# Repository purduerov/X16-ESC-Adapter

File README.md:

# Readme for X16-ESC-Adapter
This board powers the ESCs and routes signals to and from the ESCs.

Whenever you make a new part, download the datasheet and save it here _**and**_ with the part in the parts library

Always pull other people's changes before beginning to work
`git pull`

Be sure to push your changes after  working on them. Run:
1. `git add .` to add any files in this directory or a subdirectory
or `git add -u` to add any modified files
2. (Optional) `git clean -nX` to see what ignored files can be removed
	`git clean -fX` removes ignored files (Eagle backups)
3. `git commit -m "helpful commit message"` with a description of the work that you did
4. `git push` to push your work to github

Other helpful commands
* `git status` says information about modified and staged files
* `git log` shows the recent commits of the repository
* `git log filename.extension` show the recent commits for just that file
* `git checkout first-couple-letter-of-commit-id` lets you go back to a previous version
* `git checkout master` brings you back to the latest commit
* `git tag` lists the tags
* `git tag -a orderX -m "the version of the board placed for the X'th order"` tag a specific commit
* `git push --tags` needed to push tags to remote
* `git show orderX` show the commit log for the given tag
* `git checkout orderX` go back and interact with the files at the tagged commit

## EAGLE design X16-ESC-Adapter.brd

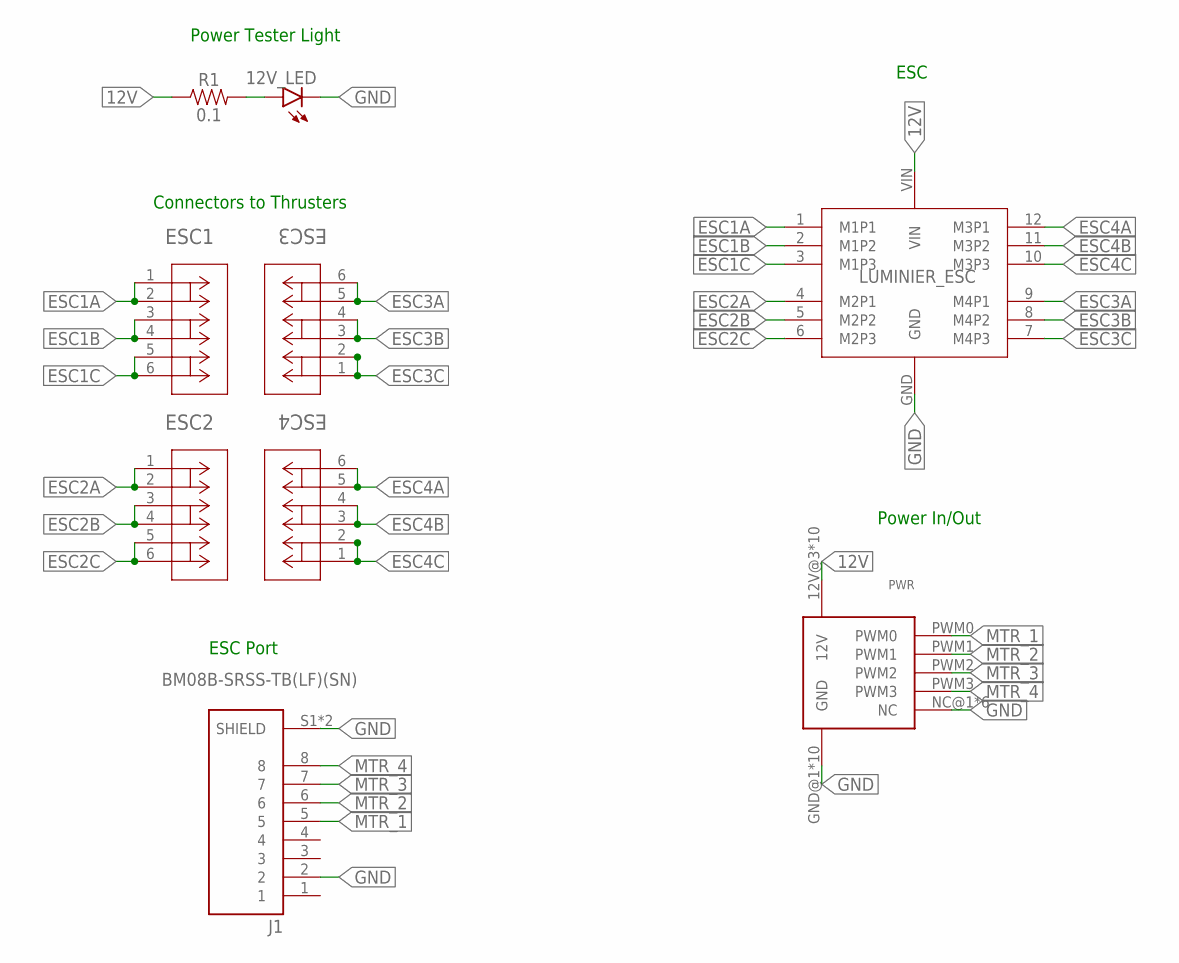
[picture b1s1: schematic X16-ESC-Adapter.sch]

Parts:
12V_LED: LEDCHIPLED_0805; CHIPLED_0805
ESC1, ESC2, ESC3, ESC4: CONN_1824750000; CONN3_1824750000_WED
J1: BM08B-SRSS-TB(LF)(SN); JST_BM08B-SRSS-TB(LF)(SN)
LUMINIER_ESC: LUMENIER
PWR: CONN_BACKPLANE_ESC_ADAPTER
R1: 0.1; 0603

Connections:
12V: LUMINIER_ESC.VIN, PWR.12V@3 (12V), PWR.12V@4 (12V), PWR.12V@5 (12V), PWR.12V@6 (12V), PWR.12V@7 (12V), PWR.12V@8 (12V), PWR.12V@9 (12V), PWR.12V@10 (12V), PWR.12V@11 (12V), PWR.12V@12 (12V), R1.1
ESC1A: ESC1.1, ESC1.2, LUMINIER_ESC.1 (M1P1)
ESC1B: ESC1.3, ESC1.4, LUMINIER_ESC.2 (M1P2)
ESC1C: ESC1.5, ESC1.6, LUMINIER_ESC.3 (M1P3)
ESC2A: ESC2.1, ESC2.2, LUMINIER_ESC.4 (M2P1)
ESC2B: ESC2.3, ESC2.4, LUMINIER_ESC.5 (M2P2)
ESC2C: ESC2.5, ESC2.6, LUMINIER_ESC.6 (M2P3)
ESC3A: ESC3.5, ESC3.6, LUMINIER_ESC.9 (M4P1)
ESC3B: ESC3.3, ESC3.4, LUMINIER_ESC.8 (M4P2)
ESC3C: ESC3.1, ESC3.2, LUMINIER_ESC.7 (M4P3)
ESC4A: ESC4.5, ESC4.6, LUMINIER_ESC.12 (M3P1)
ESC4B: ESC4.3, ESC4.4, LUMINIER_ESC.11 (M3P2)
ESC4C: ESC4.1, ESC4.2, LUMINIER_ESC.10 (M3P3)
GND: 12V_LED.C, J1.2, J1.S1 (SHIELD), J1.S2 (SHIELD), LUMINIER_ESC.GND, PWR.GND@1 (GND), PWR.GND@2 (GND), PWR.GND@3 (GND), PWR.GND@4 (GND), PWR.GND@5 (GND), PWR.GND@6 (GND), PWR.GND@7 (GND), PWR.GND@8 (GND), PWR.GND@9 (GND), PWR.GND@10 (GND), PWR.NC@1 (NC), PWR.NC@2 (NC), PWR.NC@3 (NC), PWR.NC@4 (NC), PWR.NC@5 (NC), PWR.NC@6 (NC)
MTR_1: J1.5, PWR.PWM0
MTR_2: J1.6, PWR.PWM1
MTR_3: J1.7, PWR.PWM2
MTR_4: J1.8, PWR.PWM3
unnamed: 12V_LED.A, R1.2

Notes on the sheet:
Connectors to Thrusters
Power Tester Light
Power In/Out
ESC
ESC Port

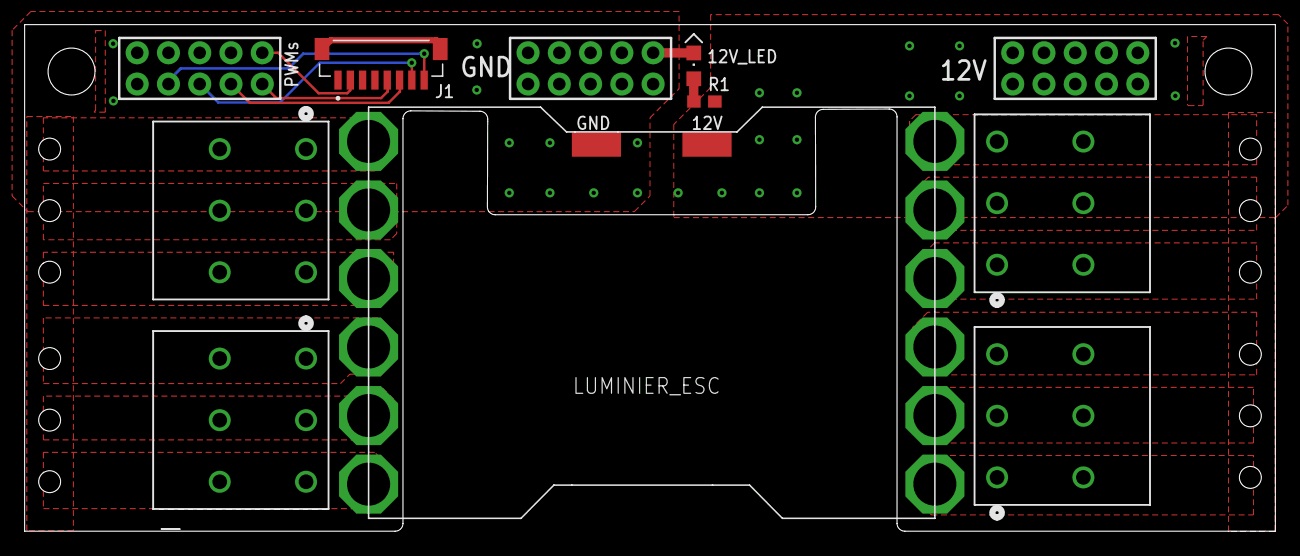
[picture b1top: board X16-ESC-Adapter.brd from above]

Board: 2 copper layers, 101.6 x 41.1 mm, 11 parts (0 on the bottom side), 19 nets.

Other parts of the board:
U$1, U$2: 6-32-HOLE

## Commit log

2023-08-30 tentative dimensions
2023-09-23 Added .gitignore file
2023-09-23 Included the needed parts
2023-10-04 Curren tprogress on schem
2023-10-04 Fixed gitignore not pulling
2023-10-04 Update X16-ESC-Adapter.brd
    10/4/23 - Started Board Circuitry
2023-10-14 Finished Layout
2023-11-02 First set of changes after alumni design review
2023-11-04 Updated (11/4)
2023-11-17 Scaffolding holes updated
    Scaffolding holes updated
2023-12-02 Finished!
2023-12-03 Actually done (this time fo real)
2023-12-07 Now actually finished for sure
2023-12-21 moved gnd trace so it doesn't overlap with pin 1 on jst
2023-12-21 added junctions + moved LED to left
2023-12-21 added pwms label
2023-12-29 Minh Update 1
2023-12-30 Create GERBER files

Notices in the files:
parts and their libraries:
SparkFun-Resistors: Licensing: Creative Commons ShareAlike 4.0 International - https://creativecommons.org/licenses/by-sa/4.0
COPYRIGHT: Copyright (C) 2023 Ultra Librarian. All rights reserved.
